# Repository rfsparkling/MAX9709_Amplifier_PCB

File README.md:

MAX9709 50W, Filterless, Spread-Spectrum, Stereo/Mono, Class D Amplifier
This is my MAX9709 amplifier project, started at 2009. Made my own PCB to evaluate the Class-D audio amplifier IC. 

I've built and tested my amplifier that time and it works. Recently redesigned it, made a smaller PCB. However not yet tested due to lack of resources.
I have bare PCBs to sell.

https://www.maximintegrated.com/en/products/analog/audio/MAX9709.html

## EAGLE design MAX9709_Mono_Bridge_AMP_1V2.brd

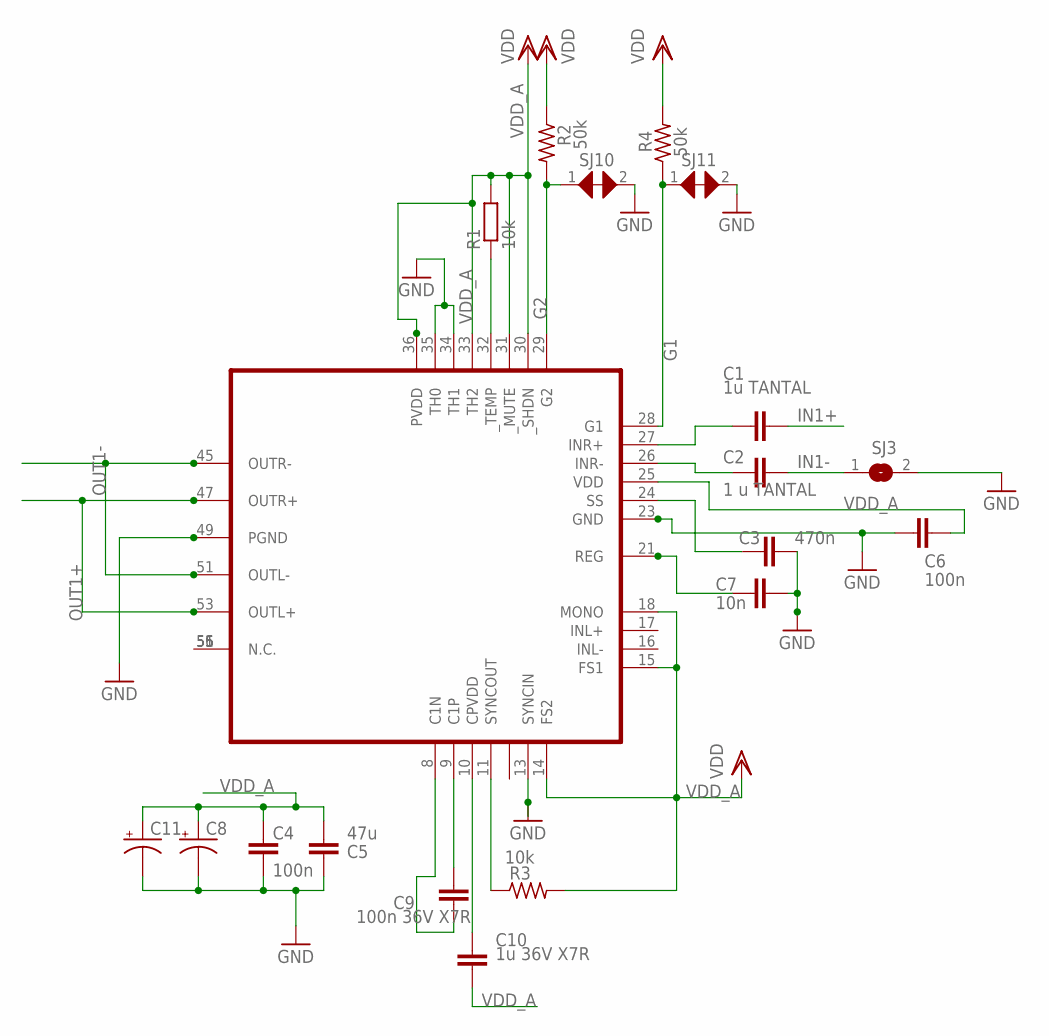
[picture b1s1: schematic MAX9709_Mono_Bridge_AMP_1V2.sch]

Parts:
C1: 1u TANTAL; 0805
C2: 1 u TANTAL; 0805
C3: 470n; C0402K
C4: 100n; 0603
C5: 47u; 0603
C6: 100n; C0402K
C7: 10n; C0402K
C8, C11: CPOL-USCT7343; CT7343
C9: 100n 36V X7R; 0805
C10: 1u 36V X7R; 0805
IC1: MAX9709; 56-QFN
R1, R3: 10k; R0402
R2, R4: 50k; R0402
SJ3: JUMPER_SMD; JUMPER_SMD_SJ
SJ10, SJ11: JUMPER_SMD_MICRO_SHORT

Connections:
G1: IC1.28 (G1), R4.1, SJ11.1
G2: IC1.29 (G2), R2.2, SJ10.1
GND: C3.2, C4.2, C5.2, C6.1, C7.2, C8.-, C11.-, IC1.2 (PGND$2), IC1.3 (PGND$3), IC1.4 (PGND$4), IC1.13 (SYNCIN), IC1.22 (GND2), IC1.23 (GND), IC1.34 (TH1), IC1.35 (TH0), IC1.39 (PGND$39), IC1.40 (PGND$40), IC1.41 (PGND$41), IC1.49 (PGND), IC1.50 (PGND$8), IC1.P$1 (GND1), IC1.P$2 (GND3), IC1.P$3 (GND4), IC1.P$4 (GND5), IC1.P$5 (GND6), IC1.P$6 (GND7), IC1.P$7 (GND8), IC1.P$8 (GND9), IC1.P$9 (GND10), IC1.P$10 (GND11), IC1.P$11 (GND12), IC1.P$12 (GND13), IC1.P$13 (GND14), IC1.P$14 (GND15), IC1.P$15 (GND16), IC1.P$16 (GND17), IC1.P$17 (GND18), IC1.P$18 (GND19), IC1.P$19 (GND20), IC1.P$20 (GND21), IC1.P$21 (GND22), IC1.P$22 (GND23), IC1.P$23 (GND24), IC1.P$24 (GND25), IC1.P$25 (GND26), SJ3.2, SJ10.2, SJ11.2
IN1+: C1.P$1 (1)
IN1-: C2.P$1 (1), SJ3.1
unnamed: C9.P$1 (1), IC1.8 (C1N)
unnamed: C9.P$2 (2), IC1.9 (C1P)
unnamed: C1.P$2 (2), IC1.27 (INR+)
unnamed: C2.P$2 (2), IC1.26 (INR-)
unnamed: IC1.32 (_TEMP), R1.1
unnamed: C10.P$2 (2), IC1.10 (CPVDD)
unnamed: IC1.11 (SYNCOUT), R3.1
OUT1+: IC1.47 (OUTR+), IC1.48 (OUTR+2), IC1.53 (OUTL+), IC1.54 (OUTL+2)
OUT1-: IC1.45 (OUTR-), IC1.46 (OUTR-2), IC1.51 (OUTL-), IC1.52 (OUTL-2)
REG: C7.1, IC1.19 (REG3), IC1.20 (REG2), IC1.21 (REG)
SS: C3.1, IC1.24 (SS)
VDD_A: C4.1, C5.1, C6.2, C8.+, C10.P$1 (1), C11.+, IC1.5 (PVDD$5), IC1.6 (PVDD$6), IC1.7 (PVDD$7), IC1.14 (FS2), IC1.15 (FS1), IC1.18 (MONO), IC1.25 (VDD), IC1.30 (_SHDN), IC1.31 (_MUTE), IC1.33 (TH2), IC1.36 (PVDD), IC1.37 (PVDD$37), IC1.38 (PVDD$38), R1.2, R2.1, R3.2, R4.2

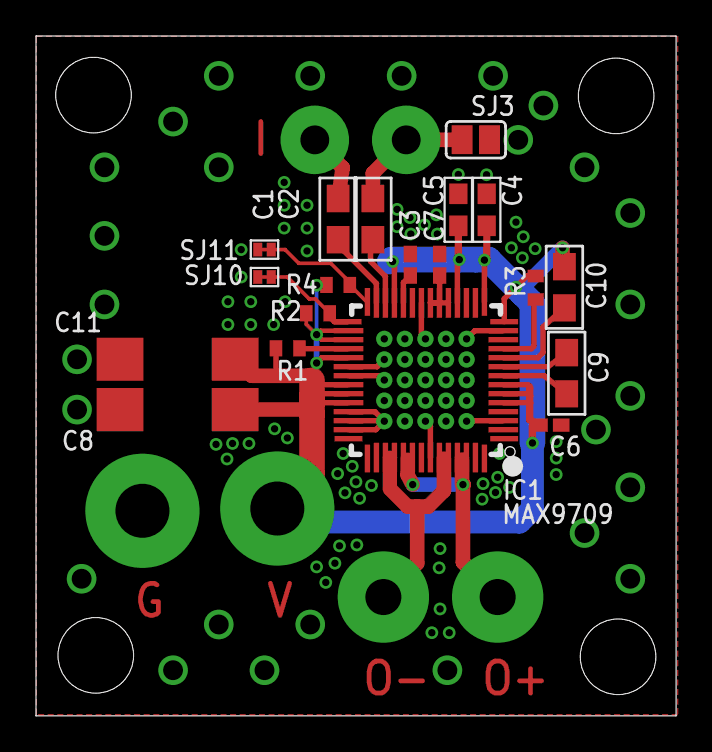
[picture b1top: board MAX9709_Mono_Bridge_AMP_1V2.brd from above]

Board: 2 copper layers, 35.6 x 37.8 mm, 19 parts (0 on the bottom side), 16 nets.

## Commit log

2015-12-16 :neckbeard: Added .gitattributes & .gitignore files
2015-12-16 adding files
2015-12-16 correction
2015-12-16 adding lic file
